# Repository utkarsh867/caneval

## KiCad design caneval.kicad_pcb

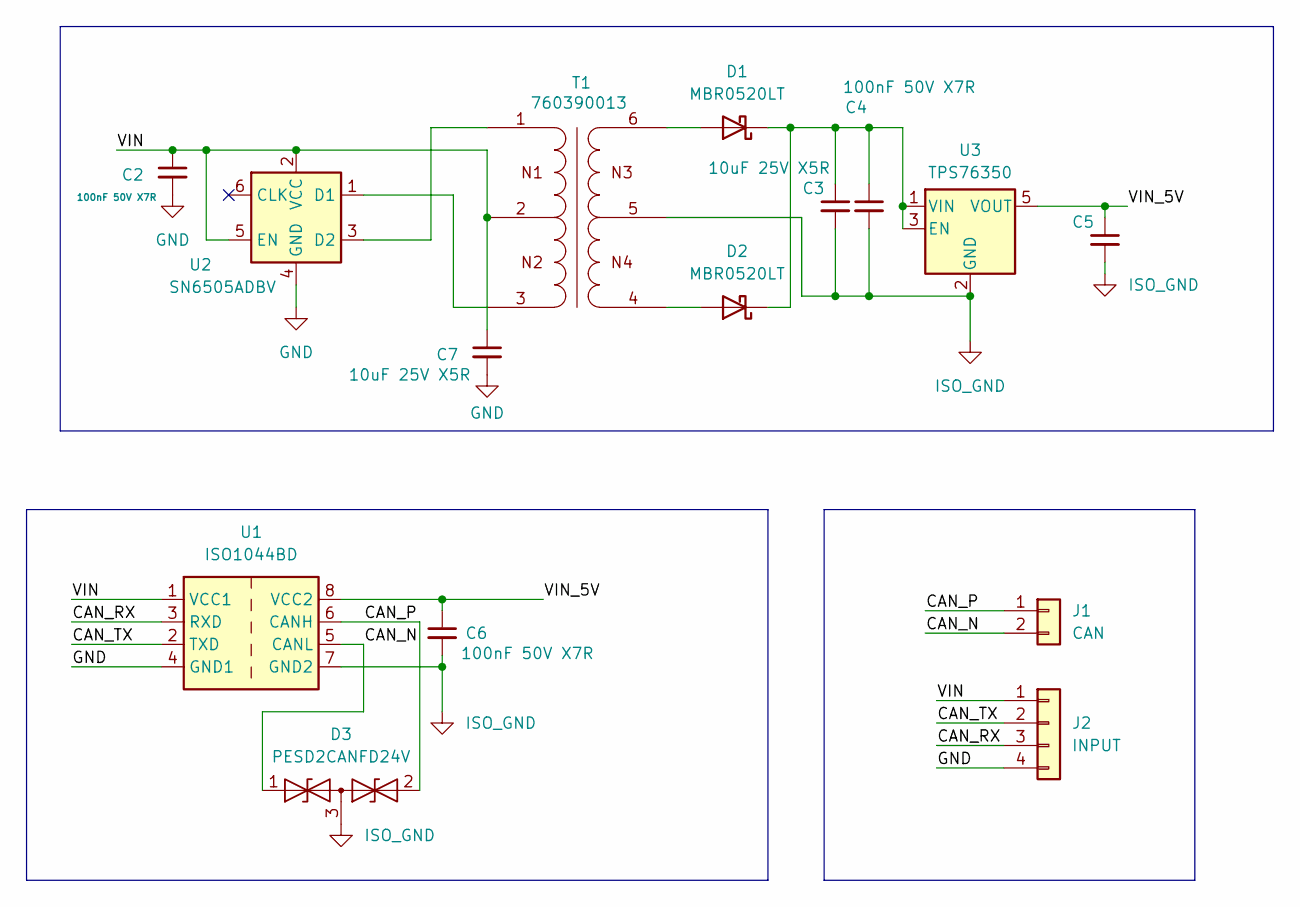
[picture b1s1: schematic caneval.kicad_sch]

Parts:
C2, C4: 100nF 50V X7R; C_0402_1005Metric
C3, C7: 10uF 25V X5R; C_0603_1608Metric
C5: C_0603_1608Metric
C6: 100nF 50V X7R; C_0402_1005Metric; JLCPCB C307331
D1, D2: MBR0520LT; D_SOD-123
D3: PESD2CANFD24V; SOT-23
J1: CAN; PhoenixContact_MCV_1,5_2-G-3.81_1x02_P3.81mm_Vertical
J2: INPUT; PhoenixContact_MCV_1,5_4-G-3.81_1x04_P3.81mm_Vertical
T1: 760390013; T_Wurth_WE-PPTI-1006; Part Number 760390013
U1: ISO1044BD; SOIC-8_3.9x4.9mm_P1.27mm
U2: SN6505ADBV; SOT-23-6
U3: TPS76350; SOT-23-5

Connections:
/CAN_N: D3.1 (A1), J1.2, U1.5 (CANL)
/CAN_P: D3.2 (A2), J1.1, U1.6 (CANH)
/CAN_RX: J2.3, U1.3 (RXD)
/CAN_TX: J2.2, U1.2 (TXD)
/VIN: C2.1, C7.1, J2.1, T1.2, U1.1 (VCC1), U2.2 (VCC), U2.5 (EN)
/VIN_5V: C5.1, C6.1, U1.8 (VCC2), U3.5 (VOUT)
GND: C2.2, C7.2, J2.4, U1.4 (GND1), U2.4 (GND)
ISO_GND: C3.2, C4.2, C5.2, C6.2, D3.3 (common), T1.5, U1.7 (GND2), U3.2 (GND)
unnamed: D1.2 (A), T1.6
unnamed: C3.1, C4.1, D1.1 (K), D2.1 (K), U3.1 (VIN), U3.3 (EN)
unnamed: D2.2 (A), T1.4
unnamed: T1.3, U2.1 (D1)
unnamed: T1.1, U2.3 (D2)

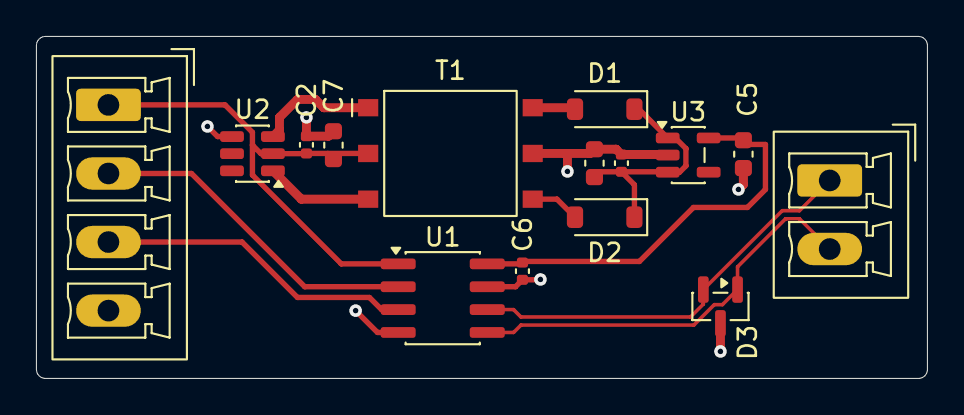
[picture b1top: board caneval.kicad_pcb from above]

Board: 2 copper layers, 49.5 x 19.0 mm, 15 parts (0 on the bottom side), 13 nets.

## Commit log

2026-06-24 Add kicad-ci stuff
2026-06-24 add enable pin connection
2026-06-24 fix path in github actions
2026-06-24 add correct docker image
2026-06-24 add pr-job test
2026-06-24 fix error in job cancel check
2026-06-24 fix job config path
2026-06-24 cleanup config
2026-06-24 remove description field
2026-06-24 fix output path
2026-06-25 fix github action branch history
